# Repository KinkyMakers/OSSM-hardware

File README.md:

# OSSM - Open Source Sex Machine

**Maintained by [Research and Desire](https://researchanddesire.com), supported by the community.**

[Read the documentation here.](https://docs.researchanddesire.com/ossm)

## What is OSSM?

**OSSM** (pronounced like "awesome") is a user-friendly, open-source sex machine designed for everyday use. Whether you're curious about sex machines or looking to build your own, OSSM provides a powerful, customizable solution you can assemble at home.

OSSM uses a servo-powered belt-driven linear rail, enabling quiet operation, high torque, and software-defined stroke and depth control at speeds up to 1 meter per second.

### Performance Specifications

| Specification | Standard (20V DC) | High Power (36V DC) |
|---------------|-------------------|---------------------|
| Force output  | 32 lbs (14 kg)    | 50 lbs (22 kg)      |
| Stroke length | 8" (20 cm)        | 8" (20 cm)          |
| Rail size     | 350mm             | 350mm               |

### Why Build an OSSM?

- **Full control** over stroke length, depth, and speed through software
- **Quiet operation** suitable for shared living spaces
- **Customization options** through community-developed mods
- **Learning opportunities** in mechanics, electronics, and computing

## Quick Links

| Resource | Description |
|----------|-------------|
| [Documentation](https://docs.researchanddesire.com/ossm) | Complete build guides, hardware specs, and software reference |
| [R+D Store](https://researchanddesire.com) | Purchase motors, PCBs, wire harnesses, and complete kits |
| [KinkyMakers Discord](https://discord.gg/VtZcudpxT6) | Community discussion, build help, and mod development |
| [FAQs](https://docs.researchanddesire.com/ossm/guides/housekeeping/faqs) | Common questions about hardware, motors, printing, and control |

---

## Building Your OSSM

For complete step-by-step instructions, see the [Build Guide](https://docs.researchanddesire.com/ossm/guides/getting-started/build-guide/step-0.0_introduction).

### Bill of Materials

For the complete parts list with supplier links, see [Required Tools and Parts](https://docs.researchanddesire.com/ossm/guides/getting-started/build-guide/step-1.0_required_tools_and_parts).

### Electronics

| Component | Description | Documentation |
|-----------|-------------|---------------|
| Motor | 57AIM30 "Gold Motor" | [Motor Documentation](https://docs.researchanddesire.com/ossm/Hardware/motor/standard-build-motor) |
| Reference Board | OSSM PCB or ESP32 Development Board | [Board Design](https://docs.researchanddesire.com/ossm/Hardware/PCB/board-design) |
| Remote | OSSM Wired Remote | [Remote Documentation](https://docs.researchanddesire.com/ossm/Hardware/standard-printed-parts/remote/introduction) |
| Wiring | JST-PH 2.0 4-Pin data cable and 16awg power wire | [Wiring Guide](https://docs.researchanddesire.com/ossm/Hardware/motor/wiring-gold-motor) |

**Power Supply:** 20-36V DC (5.5 x 2.1 Barrel Plug). A 24V 5A supply is recommended. Higher voltage (up to 36V) provides increased force.

> **Portable Option:** USB Power Banks capable of true 100W USB PD generally work well.
> - INIU Power Bank P63-E1 100W (tested, works)
> - INIU B62 Power Bank 65W (tested, powers down on high load)

### Printed Parts

For 3D printing settings and material recommendations, see [3D Printing Parts](https://docs.researchanddesire.com/ossm/guides/getting-started/build-guide/step-1.2_3d-printing-parts).

| Assembly | Parts Included | Documentation |
|----------|----------------|---------------|
| [Actuator](Printed%20Parts/Actuator/) | Body, Belt Tensioner, Threaded End Effector | [Actuator Docs](https://docs.researchanddesire.com/ossm/Hardware/standard-printed-parts/actuator/introduction) |
| [Remote](Printed%20Parts/Remote/) | Body, Knobs, Top Cover | [Remote Docs](https://docs.researchanddesire.com/ossm/Hardware/standard-printed-parts/remote/introduction) |
| [Toy Mounting](Printed%20Parts/Toy%20Mounting/) | Flange Base, Vac-U-Lock Adapters | [Toy Mounting Docs](https://docs.researchanddesire.com/ossm/Hardware/standard-printed-parts/toy-mounting/introduction) |
| [Mounting](Printed%20Parts/Mounting/) | PitClamp Mini Ring/Base, PCB Enclosure | [Mounting Docs](https://docs.researchanddesire.com/ossm/Hardware/standard-printed-parts/pitclamp/README) |
| [Stand](Printed%20Parts/Stand/) | 3030 Extrusion Base Components | [Stand Docs](https://docs.researchanddesire.com/ossm/Hardware/standard-printed-parts/stand/introduction) |
| [Radiating PitClamp Stand](Printed%20Parts/OSSM%20Mods/Radiating%20PitClamp%20Stand/) | One- and two-arm kits with a captured handle and four-color artwork | [Kit files and notes](Printed%20Parts/OSSM%20Mods/Radiating%20PitClamp%20Stand/README.md) |

Experimental parts are developed in the [KinkyMakers Discord](https://discord.gg/wrENMKb3) `#ossm-print-testing` channel.

### Hardware Components

**GT2 Pulley**
- Qty 1: 8mm Bore, 20 Tooth, 10mm Width

**GT2 Timing Belt**
- Qty 1: 10mm Width, 500mm length

**MGN12H Rail + Bearing Block**
- Qty 1: Minimum 250mm, Suggested 350mm, Maximum 550mm
- Rail length = desired maximum stroke + 180mm
- Must be MGN**12H** (H = longer bearing block for stability, 12 = 12mm rail width)

**Ball Bearings**
- Qty 6: MR115-2RS 5x11x4mm

**Fasteners**
| Qty | Part |
|-----|------|
| 8 | M3x8 Socket Cap Head Bolt |
| 2 | M3x16 Socket Cap Head Bolt |
| 1 | M3x20 Socket Cap Head Bolt |
| 7 | M3 Hex Nut |
| 3 | M5x20 Socket Cap Head Bolt |
| 1 | M5 Hex Nut |
| 4 | M5x35 Socket Cap Head Bolt |
| 4 | M5 20mm Hex Coupling Nut (or M5 Hex Nut) |

Additional hardware is required for Stand, Mounting, and Remote assemblies. See the respective [Printed Parts](Printed%20Parts/) folders for details.

---

## Assembly

**Important:** The actuator rail direction is critical for pattern accuracy and safety. The proper orientation has the threaded end to the right when looking at the front face of the actuator body (the "M" side of the OSSM text on the cover).

Your rail should extend the threaded end first when booted. If this doesn't match your build's behavior, reverse your rail's printed hardware.

### Build Resources

| Resource | Description |
|----------|-------------|
| [Complete Build Guide](https://docs.researchanddesire.com/ossm/guides/getting-started/build-guide/step-0.0_introduction) | Step-by-step documentation with images |
| [OSSM Assembly Playlist](https://youtube.com/playlist?list=PLzSK7OAu3KNQsFo6WJGT8P28lfkD3xpps) | Video tutorials for each assembly step |
| [Complete Assembly - Follow Along Guide](https://www.youtube.com/watch?v=9lVobSEw_Uw) | Full 30-minute video walkthrough |

---

## Software

For firmware flashing and configuration, see the [Software Documentation](https://docs.researchanddesire.com/ossm/Software/getting-started/introduction).

| Resource | Description |
|----------|-------------|
| [Web Flasher](https://docs.researchanddesire.com/ossm/guides/getting-started/web-flasher) | Flash firmware directly from your browser |
| [PlatformIO Setup](https://docs.researchanddesire.com/ossm/Software/getting-started/PlatformIO) | Development environment for custom builds |
| [LED Status Guide](https://docs.researchanddesire.com/ossm/Software/getting-started/LED_Status) | Understanding indicator lights |
| [StrokeEngine](https://docs.researchanddesire.com/ossm/Software/motion/stroke-engine/introduction) | Motion control library documentation |
| [Hardware Tests](https://docs.researchanddesire.com/ossm/Software/getting-started/hardware-tests) | On-device test suites for verifying peripherals, BLE, WiFi, and homing |

---

## Getting Help

- [User Guide](https://docs.researchanddesire.com/ossm/guides/getting-started/user-guide/introduction) - Operating your OSSM
- [Troubleshooting](https://docs.researchanddesire.com/ossm/guides/getting-started/user-guide/troubleshooting) - Common issues and solutions
- [Safety Information](https://docs.researchanddesire.com/ossm/guides/housekeeping/safety/introduction) - Important safety guidance
- [Discord Community](https://discord.gg/VtZcudpxT6) - Real-time community support

---

## Contributing

OSSM is open-source hardware under the [CERN Open Hardware Licence Version 2 - Strongly Reciprocal](LICENSE).

- [How to Become a Contributor](https://docs.researchanddesire.com/ossm/guides/contributing/how-to-become-a-contributor)
- [Forking the Repository](https://docs.researchanddesire.com/ossm/guides/contributing/forking)
- [Reporting Issues](https://docs.researchanddesire.com/ossm/guides/contributing/reporting-issues)
- [Roadmap](https://docs.researchanddesire.com/ossm/guides/contributing/roadmap)

---

## About

- [About Research and Desire](https://docs.researchanddesire.com/ossm/guides/housekeeping/about-research-and-desire)
- [About Kinky Makers](https://docs.researchanddesire.com/ossm/guides/housekeeping/about-kinky-makers)
- [Open Source Certification](https://docs.researchanddesire.com/ossm/guides/housekeeping/open-source/introduction)

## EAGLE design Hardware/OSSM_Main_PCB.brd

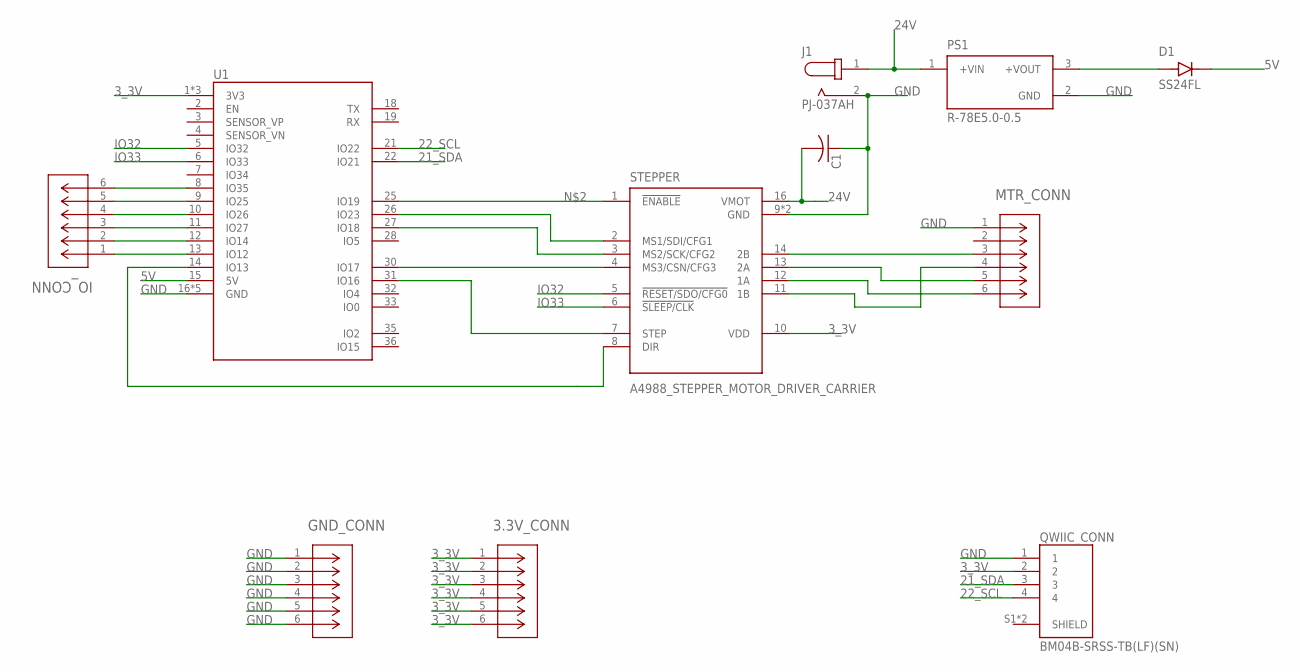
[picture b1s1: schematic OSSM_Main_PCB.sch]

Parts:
3.3V_CONN: 1792902; CONN_1792902_PXC
C1: C-US050-024X044; C050-024X044
D1: SS24FL; SODFL3617X108N
GND_CONN: 1792902; CONN_1792902_PXC
IO_CONN: 1792902; CONN_1792902_PXC
J1: PJ-037AH; CUI_PJ-037AH
MTR_CONN: 1792902; CONN_1792902_PXC
PS1: R-78E5.0-0.5; CONV_R-78E5.0-0.5
QWIIC_CONN: BM04B-SRSS-TB(LF)(SN); CONN_BM04B-SRSS-TB(LF)(SN)
STEPPER: A4988_STEPPER_MOTOR_DRIVER_CARRIER; MODULE_A4988_STEPPER_MOTOR_DRIVER_CARRIER
U1: LOLIN32_PRODUCTION

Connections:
3_3V: 3.3V_CONN.1, 3.3V_CONN.2, 3.3V_CONN.3, 3.3V_CONN.4, 3.3V_CONN.5, 3.3V_CONN.6, QWIIC_CONN.2, STEPPER.10 (VDD), U1.1 (3V3), U1.20 (3V3), U1.29 (3V3)
5V: D1.C, U1.15 (5V)
21_SDA: QWIIC_CONN.3, U1.22 (IO21)
22_SCL: QWIIC_CONN.4, U1.21 (IO22)
24V: C1.2, J1.1, MTR_CONN.2, PS1.1 (+VIN), STEPPER.16 (VMOT)
GND: C1.1, GND_CONN.1, GND_CONN.2, GND_CONN.3, GND_CONN.4, GND_CONN.5, GND_CONN.6, J1.2, MTR_CONN.1, PS1.2 (GND), QWIIC_CONN.1, STEPPER.9 (GND), STEPPER.15 (GND), U1.16 (GND), U1.17 (GND), U1.23 (GND), U1.24 (GND), U1.34 (GND)
IO32: STEPPER.5 (!RESET/SDO/CFG0), U1.5 (IO32)
IO33: STEPPER.6 (!SLEEP/CLK), U1.6 (IO33)
unnamed: D1.A, PS1.3 (+VOUT)
unnamed: STEPPER.1 (!ENABLE), U1.25 (IO19)
unnamed: STEPPER.2 (MS1/SDI/CFG1), U1.26 (IO23)
unnamed: STEPPER.3 (MS2/SCK/CFG2), U1.27 (IO18)
unnamed: STEPPER.4 (MS3/CSN/CFG3), U1.30 (IO17)
unnamed: STEPPER.7 (STEP), U1.31 (IO16)
unnamed: STEPPER.8 (DIR), U1.14 (IO13)
unnamed: MTR_CONN.6, STEPPER.12 (1A)
unnamed: MTR_CONN.5, STEPPER.13 (2A)
unnamed: MTR_CONN.4, STEPPER.11 (1B)
unnamed: MTR_CONN.3, STEPPER.14 (2B)
unnamed: IO_CONN.1, U1.13 (IO12)
unnamed: IO_CONN.2, U1.12 (IO14)
unnamed: IO_CONN.3, U1.11 (IO27)
unnamed: IO_CONN.4, U1.10 (IO26)
unnamed: IO_CONN.5, U1.9 (IO25)
unnamed: IO_CONN.6, U1.8 (IO35)

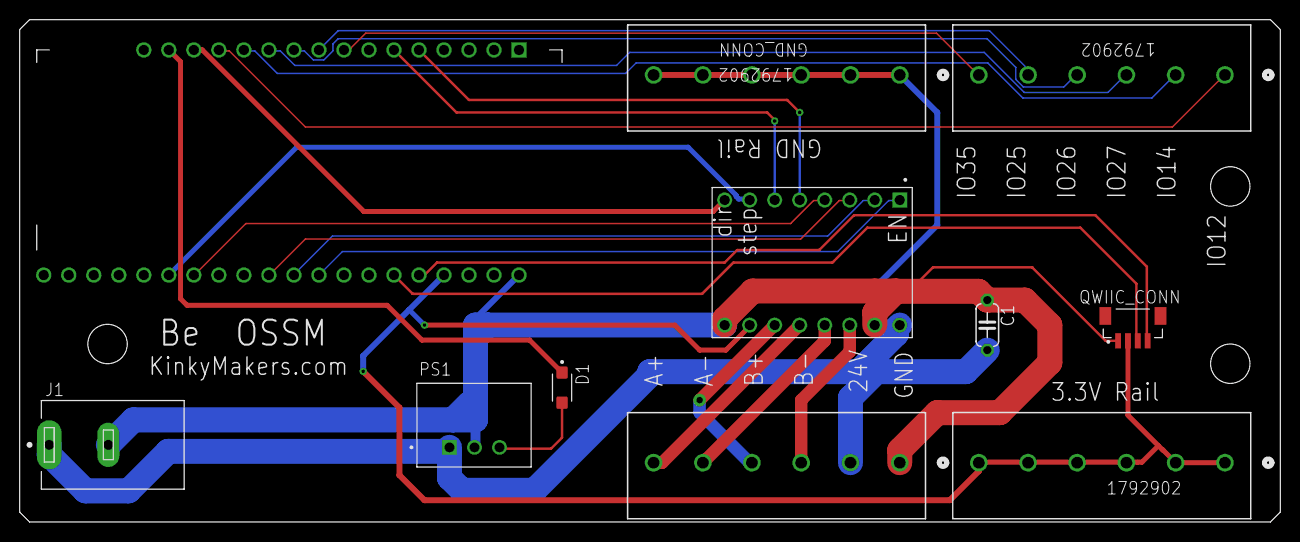
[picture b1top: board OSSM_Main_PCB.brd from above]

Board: 2 copper layers, 128.0 x 51.0 mm, 11 parts (0 on the bottom side), 25 nets.

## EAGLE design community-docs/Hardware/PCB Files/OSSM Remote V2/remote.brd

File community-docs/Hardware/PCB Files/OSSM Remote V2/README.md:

# OSSM Remote V2

This directory preserves the KiCad project, schematic, PCB layout, bill of
materials, manufacturing archives, and component-placement files for the OSSM
Remote V2.

Return to the [PCB documentation index](../README.md).

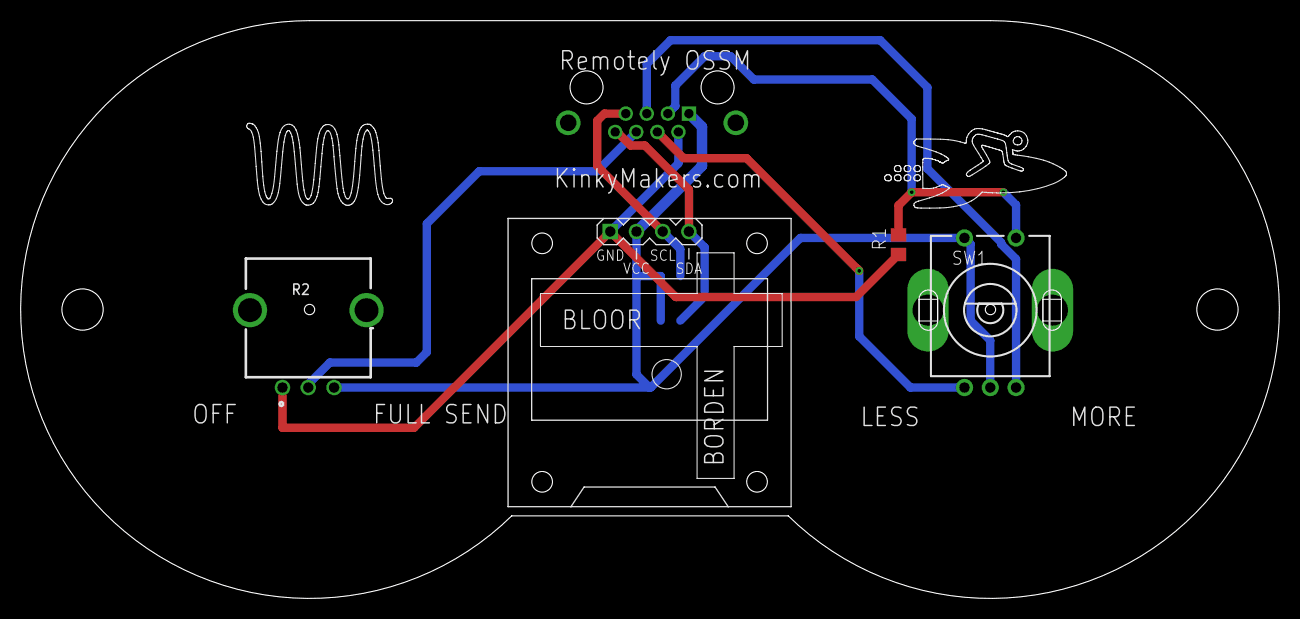
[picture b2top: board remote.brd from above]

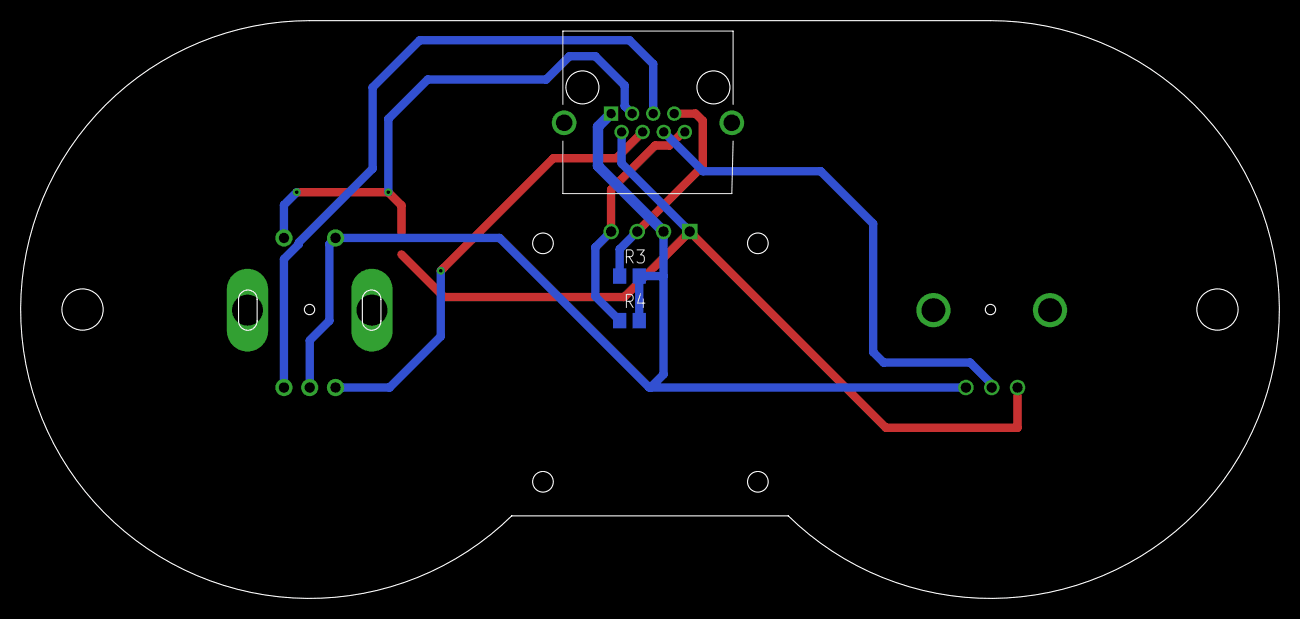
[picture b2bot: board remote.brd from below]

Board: 2 copper layers, 122.0 x 56.0 mm, 7 parts (3 on the bottom side), 8 nets.

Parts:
R1: 12k; R0805
R2: RK09L1140A2U; RK09L1140A5E
R3, R4: R0805
SW1: EC11B-V-T; EC11B-V
U$1: DISPLAY-OLED-128X64-I2C
USER_INTERFACE1: DS1128-06-S8B0P-X; DS112806S8B0PX

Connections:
3.3V: R2.3, R3.2, R4.2, SW1.C, SW1.D, U$1.2, USER_INTERFACE1.1
ANA_1: R1.2, SW1.E, USER_INTERFACE1.3
ANA_2: R2.2, USER_INTERFACE1.6
GND: R1.1, R2.1, U$1.1, USER_INTERFACE1.2
REM_GPIO_1: SW1.A, USER_INTERFACE1.4
REM_GPIO_2: SW1.B, USER_INTERFACE1.5
REM_GPIO_I2C_CLK: R3.1, U$1.3, USER_INTERFACE1.7
REM_GPIO_I2C_DATA: R4.1, U$1.4, USER_INTERFACE1.8

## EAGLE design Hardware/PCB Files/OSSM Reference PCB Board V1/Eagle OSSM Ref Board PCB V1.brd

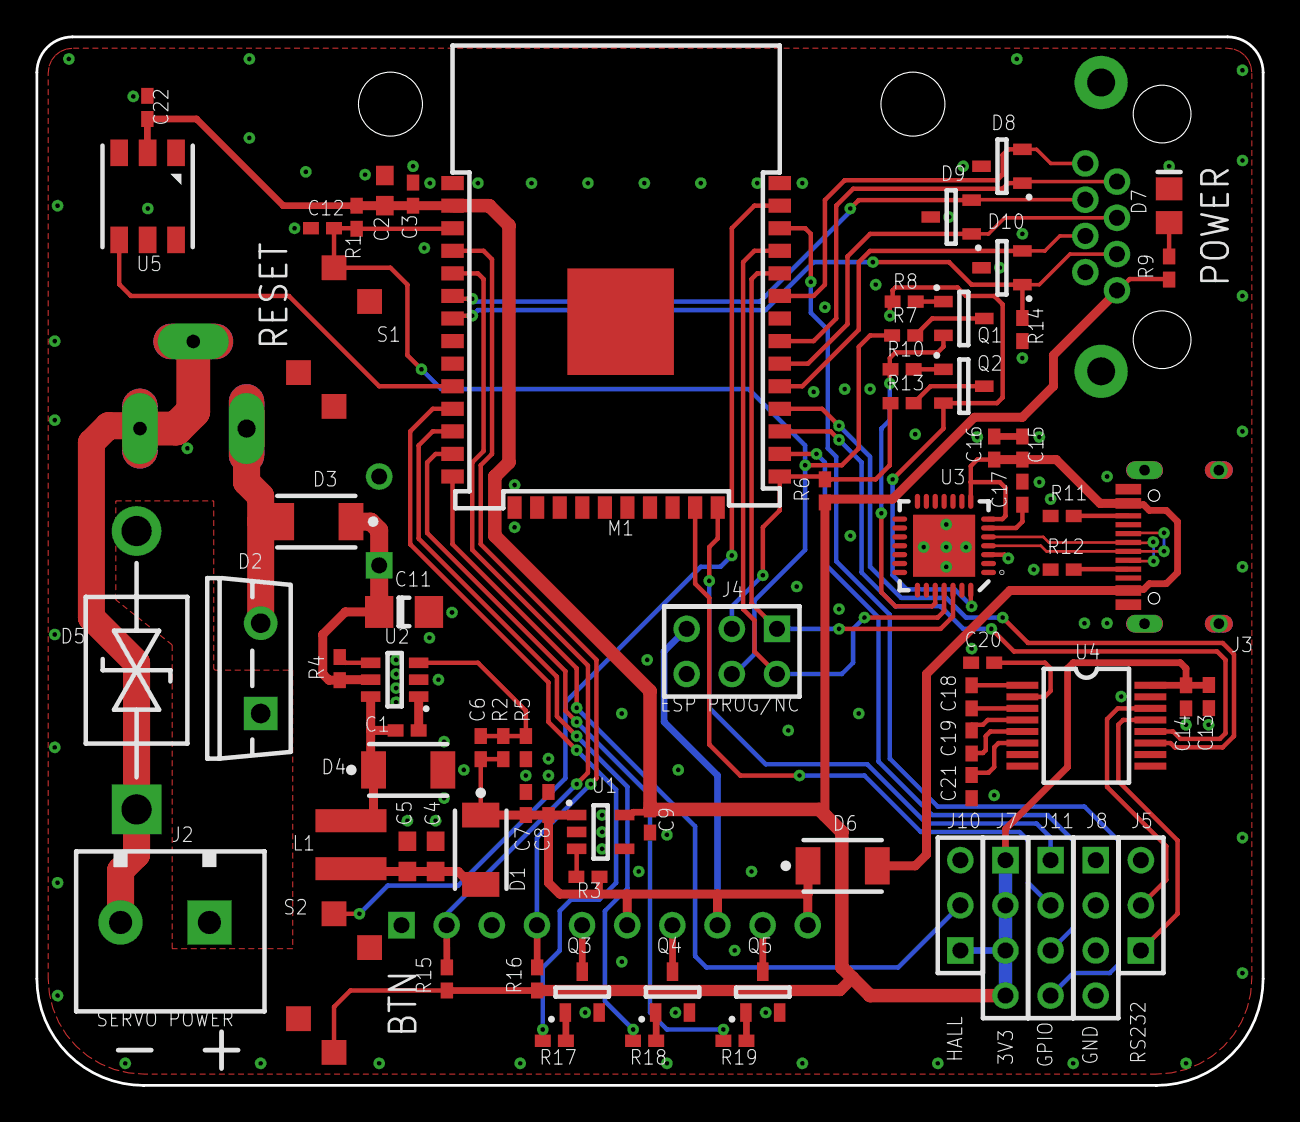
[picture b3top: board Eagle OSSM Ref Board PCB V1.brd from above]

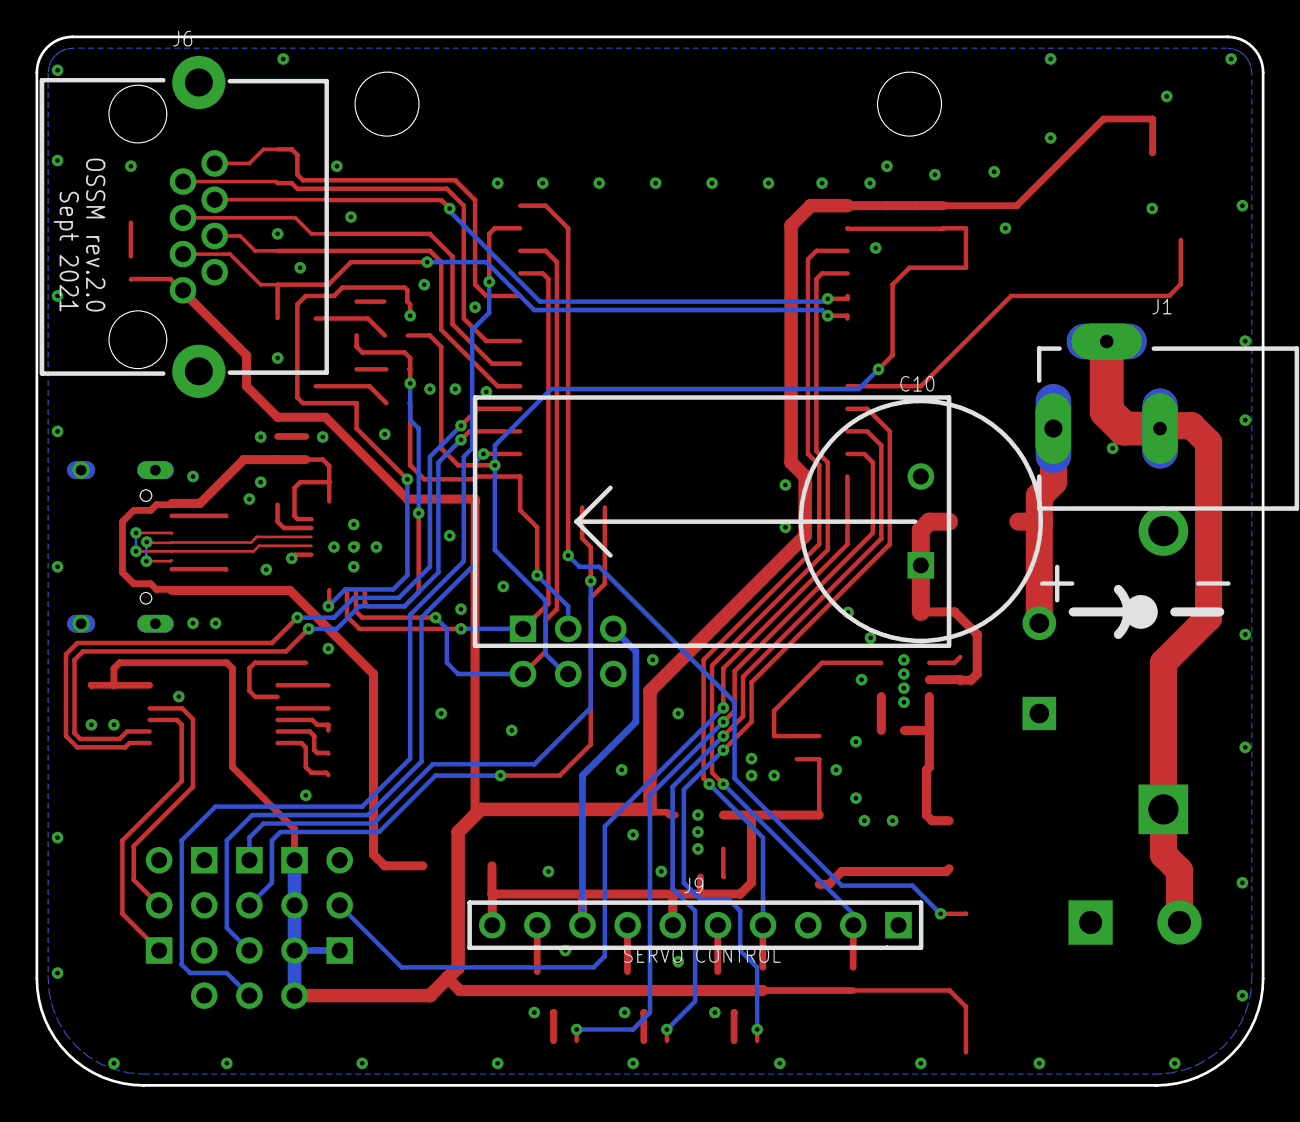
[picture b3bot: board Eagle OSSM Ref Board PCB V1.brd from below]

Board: 2 copper layers, 69.0 x 59.0 mm, 88 parts (4 on the bottom side), 63 nets.

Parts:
C1, C3, C8, C14, C16, C17, C18, C19, C20, C21: 100nF; CAP_0402
C2, C4, C5: 10uF; CAP_0603
C6: 22pF; CAP_0402
C7, C9, C13, C15, C22: 1uF; CAP_0402
C10: 1000uF/50V; CAPR-5/13.5h22
C11: 470nF; CAP_1206
C12: 10uF; CAP_0402
D1: B1100; SMA
D2: ST1060; TO-220FP-2
D3, D4, D6: B1100; SMA_D3
D5: 42V CLAMP; DO-201AD
D7: POWER; DIO_0805
D8, D9, D10: PESD1CAN 215; SOT23
J1: 24/36V IN; RAPC722X
J2: SERVO POWER; TB-1x2/5/11x9/Sc_H
J3: TYPE-C-31-M-12
J4: ESP PROG/NC; HDR-2x3
J5: RS232; HDR-1x3
J6: RJ45; DS1128-06-S8B0P-X
J7: 3V3; HDR-1x4
J8: GND; HDR-1x4
J9: SERVO CONTROL; HDR-1x10
J10: HALL; HDR-1x3
J11: GPIO; HDR-1x4
Keepout_1: 1; ROUTE_KEEPOUT_1
Keepout_2: 2; ROUTE_KEEPOUT_2
Keepout_3: 3; ROUTE_KEEPOUT_3
Keepout_4: 4; ROUTE_KEEPOUT_4
Keepout_5: 5; ROUTE_KEEPOUT_5
Keepout_6: 6; ROUTE_KEEPOUT_6
Keepout_7: 7; ROUTE_KEEPOUT_7
Keepout_8: 8; ROUTE_KEEPOUT_8
Keepout_9: 9; ROUTE_KEEPOUT_9
Keepout_10: 10; ROUTE_KEEPOUT_10
Keepout_11: 11; ROUTE_KEEPOUT_11
Keepout_12: 12; ROUTE_KEEPOUT_12
L1: 10uH; VLS4012E
M1: ESP32-WROOM-32D; ESP-WROOM-32
Q1, Q2, Q3, Q4, Q5: BC817; SOT23
R1, R3, R4, R5, R6, R8, R10, R14, R15, R16: 10K; RES_0402
R2: 54.9K; RES_0402
R7, R13: 100R; RES_0402
R9, R17, R18, R19: 220R; RES_0402
R11, R12: 5.1K; RES_0402
S1, S2: K2-1107ST-A4SW-06; Sunrom_1P1T_switch
U1: ME6211C33; SOT23-5
U2: LMR14006; SOT23-6
U3: CP2102; QFN-28/5x5x0.5
U4: SP3232E; SSOP-16
U5: WS2813

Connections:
!DIR: M1.12, R18.2
!ENA: M1.11, R17.2
!PUL: M1.13, R19.2
ALM: J9.2, M1.5, R15.1
ANA1: D10.1, J6.3, M1.7, R14.2
ANA2: D9.2, J6.6, M1.6
ESP_EN: C12.1, J4.4, M1.3, R1.2, R7.2, S1.1
ESP_RXD: J4.1, M1.34, U3.26
ESP_TXD: J4.2, M1.35, U3.25
GND: C2.2, C3.2, C4.2, C5.2, C7.2, C8.2, C9.2, C10.2, C11.2, C12.2, C13.2, C14.2, C15.2, C16.2, C17.2, C20.2, C21.1, C22.2, D4.2, D5.1, D7.1, D8.3, D9.3, D10.3, J1.2, J1.3, J2.2, J3.A1B12, J3.B1A12, J3.GND1, J3.GND2, J3.GND3, J3.GND4, J4.6, J5.3, J6.2, J6.9, J6.10, J8.1, J8.2, J8.3, J8.4, J9.1, J9.3, J10.3, M1.1, M1.15, M1.38, M1.39, Q3.2, Q4.2, Q5.2, R5.1, R11.1, R12.1, R14.1, S1.2, S1.3, S1.4, U1.2, U2.2, U3.3, U3.29, U4.15, U5.5
HALL: J10.2, M1.14
IO0: J4.3, M1.25, R6.1, R13.2
IO2: J11.1, M1.24
IO4: J11.3, M1.26
IO15: J11.2, M1.23
IO22: J11.4, M1.36
Net_0: D2.2, D3.2, J1.1
Net_3: C4.1, C5.1, D1.2, L1.2
Net_6: Q1.1, R8.2
Net_12: C17.1, U3.6
Net_23: Q2.1, R10.2
Net_24: R3.1, U1.3
Net_25: Q1.2, R10.1, U3.24
Net_26: Q2.2, R8.1, U3.28
Net_32: R4.1, U2.4
Net_33: C1.1, U2.1
Net_34: C1.2, D4.1, L1.1, U2.6
Net_35: C6.2, R2.1, R5.2, U2.3
Net_37: J9.9, Q5.3
Net_38: J9.7, Q4.3
Net_39: J9.5, Q3.3
Net_40: Q3.1, R17.1
Net_41: Q4.1, R18.1
Net_42: Q5.1, R19.1
Net_47: C18.1, U4.1
Net_48: C18.2, U4.3
Net_49: C19.1, U4.4
Net_50: C19.2, U4.5
Net_52: J5.1, U4.13
Net_53: J5.2, U4.14
Net_54: C20.1, U4.2
Net_60: D2.1, D5.2, J2.1
Net_61: C21.2, U4.6
Net_62: D7.2, R9.1
Net_74: J3.B5, R11.2
Net_75: J3.A5, R12.2
Net_76: Q2.3, R13.1
Net_77: Q1.3, R7.1
PED: J9.4, M1.4, R16.1
REM_GPIO1: D10.2, J6.4, M1.29
REM_GPIO2: D9.1, J6.5, M1.30
REM_I2C_SCL: D8.1, J6.7, M1.31
REM_I2C_SDA: D8.2, J6.8, M1.33
RGB: M1.10, U5.4
RS232_RXD: M1.27, U4.12
RS232_TXD: M1.28, U4.11
SW: M1.37, S2.1
USB_D_N: J3.A7, J3.B7, U3.5
USB_D_P: J3.A6, J3.B6, U3.4
VDD_3V3: C2.1, C3.1, C9.1, C13.1, C14.1, C22.1, J6.1, J7.1, J7.2, J7.3, J7.4, J10.1, M1.2, R1.1, R6.2, R9.2, R15.2, R16.2, S2.2, U1.5, U4.16, U5.2
VDD_5V0: C6.1, C7.1, C8.1, D1.1, D6.1, J4.5, J9.6, J9.8, J9.10, R2.2, R3.2, U1.1
VDD_36V: C10.1, C11.1, D3.1, R4.2, U2.5
VDD_USB: C15.1, C16.1, D6.2, J3.A4B9, J3.B4A9, U3.7, U3.8

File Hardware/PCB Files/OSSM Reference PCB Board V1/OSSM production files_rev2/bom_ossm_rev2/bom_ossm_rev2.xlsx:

RefDes | Value | Name | Pattern | Quantity | NOTES
C1, C3, C8, C14, C16, C17, C18, C19, C20, C21 | 100nF | X5R or X7R/16V/0402 | CAP_0402 | 10
C2, C4, C5 | 10uF | X5R or X7R/10V/0603 | CAP_0603 | 3
C6 | 22pF | C0G or NP0/16V/0402 | CAP_0402 | 1
C7, C9, C13, C15, C22 | 1uF | X5R or X7R/10V/0402 | CAP_0402 | 5
C10 | 1000uF/50V | ECA-1HM102 | CAPR-5/13.5h22 | 1 | Mount horizontally
C11 | 470nF | X5R or X7R/100V/1206 | CAP_1206 | 1
C12 | 10uF | X5R or X7R/16V/0603 | CAP_0402 | 1
D1, D3, D4, D6 | B1100 | B1100-13-F | SMA | 4
D2 | ST1060 | ST1060 | TO-220FP-2 | 1 | Confirm orientation before soldering
D5 | 42V CLAMP | 1.5KE51CA | DO-201AD | 1
D7 | POWER | BLUE LED 0805 | DIO_0805 | 1
D8, D9, D10 | PESD1CAN 215 | PESD1CAN 215 | SOT23 | 3
J1 | 24/36V IN | RAPC722X | RAPC722X | 1
J2 | SERVO POWER | WJ128V-5.0-2P | TB-1x2/5/11x9/Sc_H | 1
J3 | TYPE-C-31-M-12 | TYPE-C-31-M-12 | TYPE-C-31-M-12 | 1
J4 | ESP PROG | HDR-2x3/0.1 male/vertical | HDR-2x3 | 1
J5 | RS232 | HDR-1x3/0.1 male/vertical | HDR-1x3 | 1
J6 | RJ45 | DS1128-06-S8B0P-X | DS1128-06-S8B0P-X | 1
J7 | 3V3 | HDR-1x4/0.1 male/vertical | HDR-1x4 | 1
J8 | GND | HDR-1x4/0.1 male/vertical | HDR-1x4 | 1
J9 | SERVO CONTROL | HDR-1x10 | HDR-1x10 | 1
J10 | HALL | HDR-1x3/0.1 male/vertical | HDR-1x3 | 1
J11 | GPIO | HDR-1x4/0.1 male/vertical | HDR-1x4 | 1
L1 | 10uH | WPN4020H100MT | VLS4012E | 1
M1 | ESP32-WROOM-32D | ESP32-WROOM-32D | ESP-WROOM-32 | 1
Q1, Q2, Q3, Q4, Q5 | BC817 | BC817 | SOT23 | 5
R1, R3, R4, R5, R6, R8, R10, R14, R15, R16 | 10K | 1%/0402 | RES_0402 | 10
R2 | 54.9K | 1%/0402 | RES_0402 | 1
R7, R13 | 100R | 1%/0402 | RES_0402 | 2
R9, R17, R18, R19 | 220R | 1%/0402 | RES_0402 | 4
R11, R12 | 5.1K | 1%/0402 | RES_0402 | 2
S1, S2 |  | K2-1107ST-A4SW-06 | Sunrom 1P1T switch | 2
U1 | ME6211C33 | ME6211C33M5G-N or RT9080-33GJ5 | SOT23-5 | 1
U2 | LMR14006 | LMR14006YDDCR | SOT23-6 | 1
U3 | CP2102 | CP2102-GMR | QFN-28/5x5x0.5 | 1
U4 | SP3232E | SP3232EEA-L/TR or MAX232ECPWR | SSOP-16 | 1
U5 | WS2813 | WS2813 | WS2813 | 1

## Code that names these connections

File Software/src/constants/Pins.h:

#ifndef OSSM_SOFTWARE_PINS_CPP
#define OSSM_SOFTWARE_PINS_CPP

/**
 * Pin definitions for the OSSM
 *
 * These are all the hardware pins used by the OSSM.
 * These include pin definitions for Drivers, Buttons and Remotes
 *
 * To reference a pin, import this file and use the Pins namespace as follows:
 *
 * ```cpp
 * #include "constants/pins.cpp"
 *
 * Pins::button_in
 * Pins::Driver::motorStepPin
 * Pins::Homing::stopPin
 *
 * ```
 */

namespace Pins {

    namespace Display {
        // This pin is used by u8g2 to reset the display.
        // Use -1 if this is shared with the board reset pin.
        constexpr int oledReset = -1;

        // Pin used by RGB LED
        constexpr int ledPin = 25;
    }

    namespace Driver {
        constexpr int currentSensorPin = 36;

        // Pin that pulses on servo/stepper steps - likely labelled PUL on
        // drivers.
        constexpr int motorStepPin = 14;
        // Pin connected to driver/servo step direction - likely labelled DIR on
        // drivers. N.b. to iHSV57 users - DIP switch #5 can be flipped to
        // invert motor direction entirely
        constexpr int motorDirectionPin = 27;
        // Pin for motor enable - likely labelled ENA on drivers.
        constexpr int motorEnablePin = 26;

        // define the IO pin the emergency stop switch is connected to
        constexpr int stopPin = 19;
        // define the IO pin where the limit(homingStart) switch(es) are
        // connected to (switches in series in normally open setup) Switches
        // wired from IO pin to ground.
        constexpr int limitSwitchPin = 12;
    }

    namespace Wifi {
        // Pin for Wi-Fi reset button (optional)
        constexpr int resetPin = 23;
    }

    namespace GPIO {
        constexpr int pin1 = 2;
        constexpr int pin2 = 15;
        constexpr int pin3 = 22;
        constexpr int pin4 = 33;
    }

    /** These are configured for the OSSM Remote - which has a screen, a
     * potentiometer and an encoder which clicks*/
    namespace Remote {

        constexpr int speedPotPin = 34;

        // This switch occurs when you press the right button in.
        // With the current state of the code this will send out a "ButtonPress"
        // event automatically.
        constexpr int encoderSwitch = 35;

        // The rotary encoder requires at least two pins to function.
        constexpr int encoderA = 18;
        constexpr int encoderB = 5;
        constexpr int encoderPower =
            -1; /* Put -1 of Rotary encoder Vcc is connected directly to 3,3V;
                   else you can use declared output pin for powering rotary
                   encoder */

#ifdef AJ_DEVELOPMENT_HARDWARE
        constexpr int displayData = 21;
        constexpr int displayClock = 22;
#else
        constexpr int displayData = 21;
        constexpr int displayClock = 19;
#endif
        constexpr int encoderStepsPerNotch = 2;
    }
}

#endif  // OSSM_SOFTWARE_PINS_CPP

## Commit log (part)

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2026-02-24 Temporary patch
2026-02-24 docs: sync ossm documentation from docs repo
2026-02-25 Go to point pattern for stroke engine.
2026-02-25 Same issue... any motion is spamming nimble updates to connected devices.
2026-02-25 Add detail to MQTT payload
2026-02-25 Consolidated streaming code updates
2026-02-25 Better default buffer
2026-02-27 Reset queue when launching streaming mode
2026-02-28 Faster homing, with userconfig for where the device should park afterwards.
2026-03-01 4x Current, but 4x faster
2026-03-02 Fix MQTT local sync
2026-03-02 Fix - does connect
2026-03-02 Fix and fingerprint
2026-03-02 Unneeded movement with new homing code
2026-03-02 Latency Characteristic
2026-03-03 docs: migrate SaladDressing mod content to documentation site
    - Add motor-cover.mdx and dp-attachment.mdx pages with hero images
    - Enrich capstan.mdx with MGN12H vs HG20 comparison, tabbed BOMs,
    inline fastener lists, assembly guide links, and full CAD file links
    - Add "Printed parts and CAD files" sections with GitHub links to all
    STEP/3MF/STL files across suction-cup-bracket, weight-plate, and
    quick-change-toy-mount pages
2026-03-03 docs: migrate legacy JPGs to webp and remove source Pictures/ directories
    - Convert additional detail/angle photos to webp and co-locate in docs _images/
    - dp-attachment-top.webp (bracket top-down view)
    - motor-cover-rear.webp, motor-cover-back.webp (heatsink angles)
    - capstan-hg20-front.webp, capstan-hg20-side.webp (HG20 overview shots)
    - Add new images to motor-cover, dp-attachment, and capstan MDX pages
    - Delete all 54 legacy JPGs from Printed Parts Pictures/ directories
2026-03-03 fix imports
2026-03-03 restore mermaid controls
2026-03-03 Simplify Docs and add MakerWorld Links
2026-03-03 Restore some material tips
2026-03-03 Remove react import
2026-03-03 Characteristic doc
2026-03-04 Basic CSV support
2026-03-04 spacing
2026-03-06 WIP commit
2026-03-09 documentation and critical bug fix
2026-03-09 removed power saving since the OSSM does not run on battery and it was causing the OSSM setup connection to fail
2026-03-09 --no-docs Simple bug fix, no UI changes
2026-03-09 String compare
2026-03-10 Display Tests
2026-03-10 Add display documentation section with UI library docs
    Move display service docs to a dedicated Display section and add
    documentation for the lib/ui rendering library covering TextPages,
    strings, icons, logos, and visual test infrastructure.
    Made-with: Cursor
2026-03-10 temp
2026-03-10 AUTO: Version bump 1.0.12
2026-03-10 Added is-paired polling to the backend so that the screen confirms the successful pairing after the user enters the pairing code on the UI
2026-03-11 AUTO: Version bump 1.0.13
2026-03-11 AUTO: Version bump 1.0.14
2026-03-11 RAD-1957
2026-03-11 Fix MQTT connection and icons
2026-03-11 shortened the URL to make the qr code work (less characters)
2026-03-11 fix icons
2026-03-11 Added pairing loading screen so the UI doesn't seem to freeze
2026-03-11 Added return text + consolidated all the pages to TextPages file (minor refactor)
2026-03-11 payload tests
2026-03-11 Commented out the polling code
2026-03-11 AUTO: Version bump 1.0.15
2026-03-14 Pattern page fix
2026-03-14 Fix and move link
2026-03-16 Reverse setting bug fix
2026-03-16 AUTO: Version bump 1.0.16
2026-03-16 Buffer state and loop
2026-03-16 Not depth
2026-03-20 initial hw test setup
2026-03-23 UPdated the tests to reuse code and not write it's own hardware control functions
2026-03-23 Updated the platformio.ini file to enable the newly added tests
2026-03-23 Undoing wronfgul update to the .ini file
2026-03-23 Added developer documentation
2026-03-23 Minor update to the readme.md to link to the new test pae
2026-03-23 Add go:restart and go:update BLE commands to OSSM firmware
2026-03-23 Fix hardware test homing slamming into hard stops by suppressing verbose GPIO logs
    Without esp_log_level_set(gpio, ESP_LOG_WARN), the ESP-IDF GPIO/ADC
    drivers emit debug logs on every analogRead() call during the homing
    current-sensing loop. Each log blocks on Serial output, starving the
    loop and delaying stall detection — causing the motor to grind against
    the hard stops for hundreds of milliseconds before stopping.
    Production (main.cpp) already suppresses these logs. Adding the same
2026-03-24 AUTO: Version bump 1.0.17
2026-03-24 AUTO: Version bump 1.0.18
2026-03-24 ALl unit tests now pass
2026-03-25 AUTO: Version bump 1.0.19
2026-03-25 Phase 2 cont.: updating simple penetration to work with the radr
2026-03-26 Phase 3.2.0: Aded eFuse MAX hex fielf to BLE pairing charactarestic value, backward-compatible
2026-03-30 Undoing accidental git commit
2026-03-30 AUTO: Version bump 1.0.20
2026-03-30 Remove build artifacts and broken submodule from main
    Removes files that were accidentally included in PR #262:
    - Software/components/esp_littlefs (submodule ref with no .gitmodules)
    - Software/dependencies.lock
    - Software/sdkconfig.development
    - Reverts compile_commands.json to pre-merge state
    The esp_littlefs submodule reference was causing CI checkout failures.
2026-03-30 AUTO: Version bump 1.0.21
2026-03-30 Release workflow
2026-03-30 AUTO: Version bump 1.0.22
2026-03-30 AUTO: Version bump 1.0.23
2026-04-01 AUTO: Version bump 1.0.24
2026-04-02 Added Picatinny Rail Mod under /Printed Parts/OSSM Mods/LaikaTheHuskie's Mods
2026-04-04 Early draft of pattern control
2026-04-08 Create OSSM Universal Toy Mounting
    Universal Mounting structure for mounting toys to the OSSM
2026-04-09 Uploaded Work in progress mounting plates and attachments
2026-04-09 Added New Plates,
2026-04-11 Added some hardware, removed some redundant parts
2026-04-11 added gridfinity nut and bolt holders
2026-04-11 Fixed some errors in plates and added missing holes in in a backplate that was missing it
2026-04-13 multiplate WIP added
2026-04-19 Before installing library
2026-04-19 Ok.. we're using spline.h
2026-04-26 Before trying acceleration control
2026-04-27 feat(funscript-player): add built-in example funscript loader (RAD-1897)
    Adds a button under the funscript file picker that loads a short, built-in
    example funscript (slow -> medium -> fast strokes) so new users can test
    the player and verify their OSSM is responding correctly without first
    needing to source a script from elsewhere.
    Linear: https://linear.app/researchanddesire/issue/RAD-1897
2026-04-27 fix(funscript-player): address RAD-2053 safety + UX issues
    Improve the OSSM funscript player to fix three of the four problems
    reported in RAD-2053:
    1. Android video picker (Issue 1): drop accept="video/*" so the
    system picker opens the full file browser instead of forcing the
    user into the Photos / Gallery app, which hid files on network
    drives.
2026-04-28 fix(funscript-player): hold reverse/simple in refs to defeat stale closure (RAD-1993)
    The Funscript Player runs a setInterval at 2ms that captured a stale
    React closure of `syncFunscript`. After toggling Reverse (or rapid
    play/pause around it), the running interval could keep emitting
    non-reversed positions for ~1-2 seconds before "fixing itself".
    This switches `isReverse` and `isSimple` to ref-mirrored values so
    each sync tick reads the current toggle. The setInterval is also
2026-04-29 Feature to rename OSSM
2026-04-29 Shorter name
2026-04-30 8 Characters
2026-04-30 Even better homing
2026-04-30 Double tap all instrokes
2026-04-30 Only bump twice if stroke is short
2026-04-30 Pin to 2.4 as 2.5 is currently incompatible
2026-04-30 Incorrect test result
2026-05-01 Check in case of mid session stiction
2026-05-03 Before reviewing public PRS
2026-05-03 Reboot after rename
2026-05-05 Add state characteristic read callback for live positionMm
    The state characteristic's notify path only fires when the fingerprint
    changes (settings, state-machine state, pattern, sessionId). The
    fingerprint excludes positionMm, so a remote BLE client that polls via
    readValue() gets stale position data between settings changes — the
    characteristic buffer is only updated when the fingerprint changes.
    This callback runs getCurrentState() on each read so polling clients
2026-05-11 AUTO: Version bump 1.0.25
2026-05-17 Bump axios from 1.10.0 to 1.13.2 in /Documentation
    Bumps [axios](https://github.com/axios/axios) from 1.10.0 to 1.13.2.
    - [Release notes](https://github.com/axios/axios/releases)
    - [Changelog](https://github.com/axios/axios/blob/v1.x/CHANGELOG.md)
    - [Commits](https://github.com/axios/axios/compare/v1.10.0...v1.13.2)
    ---
    updated-dependencies:
2026-05-23 clean up
2026-05-23 AUTO: Version bump 1.0.26
2026-05-23 remove supabase
2026-05-23 AUTO: Version bump 1.0.27
2026-05-23 master deploy fix
2026-05-23 AUTO: Version bump 1.0.28
2026-05-25 build: bank stale local build-config (19d stale, no competing path)
    - platformio.ini: silence int-in-bool-context errors, pin espressif32@6.3.2
    - sdkconfig.development: regenerated to current ESP-IDF defaults
    - dependencies.lock: idf 4.4.4 (target esp32)
    Banked per CLAUDE.md stale-WIP-as-canonical rule (file mtime 19d, no
    upstream commits touched these paths since).
2026-05-28 for review, still choppy
2026-06-03 dev, no stepper
2026-06-04 fix streaming zero division
2026-06-14 Add direction change characteristic and user config service
2026-06-14 Fixes mid-rail logic. Aligns with other modes
2026-06-14 Test fixes
2026-06-16 Make not homed part of emergency stop, and standardize on that behavior when leaving a mode
2026-06-17 --no-docs fixing ota, should be invisible to users
2026-06-17 AUTO: Version bump 1.0.29
2026-06-18 AUTO: Version bump 1.0.30
2026-06-18 AUTO: Version bump 1.0.31

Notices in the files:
parts and their libraries:
COPYRIGHT: Copyright (C) 2018 Accelerated Designs. All rights reserved
diy-modules: Released under the Creative Commons Attribution 4.0 International License: http://creativecommons.org/licenses/by/4.0
